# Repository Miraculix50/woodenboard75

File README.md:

# Wooden Keyboard
An ISO-DE 75 % keyboard with a wooden case and knob.

It's definitely not perfect and I'm sure it could be optimized, but for me it's working great.
Feel free to [build it yourself](#parts).

## Parts
### PCB
* [0xcb Helios with MillMax pins and IC-Sockets (MCU) x1](https://keeb.supply/products/0xcb-helios?variant=f57eeaae-cae7-4b2d-b5ac-bef47a280a65)
* [Hotswap sockets x83](https://keeb.supply/products/kailh-hotswap-sockets)
* [THT diodes x84](https://keeb.supply/products/tht-diodes)
* [Reset button x1](https://keeb.supply/products/2-pin-reset-button)
* [EC11 rotary encoder x1](https://keeb.supply/products/pec11r-4220f-s0024)

**Base version:**
* Base-version PCB (when ordering, upload the [gerber files](/pcb/kicad/woodenboard75/production/keyboard.zip))

**RGB version:**
* RGB-version PCB (when ordering, upload the [gerber files](/pcb/kicad/woodenboard75_rgb/production/keyboard.zip))
* SK6812 MINI-E LEDs x83
* 330 Ω resistor x1
* 100 nF capacitor (SMD 0603) x83
* 22 µF capacitor (SMD 1206) x1

### Keys
* [Switches x83](https://keeb.supply/products/invokeys-matcha-reserve-switches)
* [Keycaps for 75%-layout](https://monacokeys.de/products/monacokeys-mk-retro-beige-pbt-keycap-set)

### Wooden case & knob

CAD files are available in the `/cad` folder (`.step` and `.shapr` format).
Pay attention to the different versions, since the RGB-version of the PCB is not compatible with the base version of the bottom case.

* Bar magnets (4mm diameter + 8mm height) x8
* Top case
* Bottom case
* Knob

> All links are just examples.

## Firmware

This keyboard uses the [QMK Firmware](https://qmk.fm). To get started see the [QMK docs](https://docs.qmk.fm/).

Note that you have to copy the contents of `qmk/keyboards/` to your local qmk clone / fork.

## Images

</img> </img> </img> </img> </img> </img> </img> </img>

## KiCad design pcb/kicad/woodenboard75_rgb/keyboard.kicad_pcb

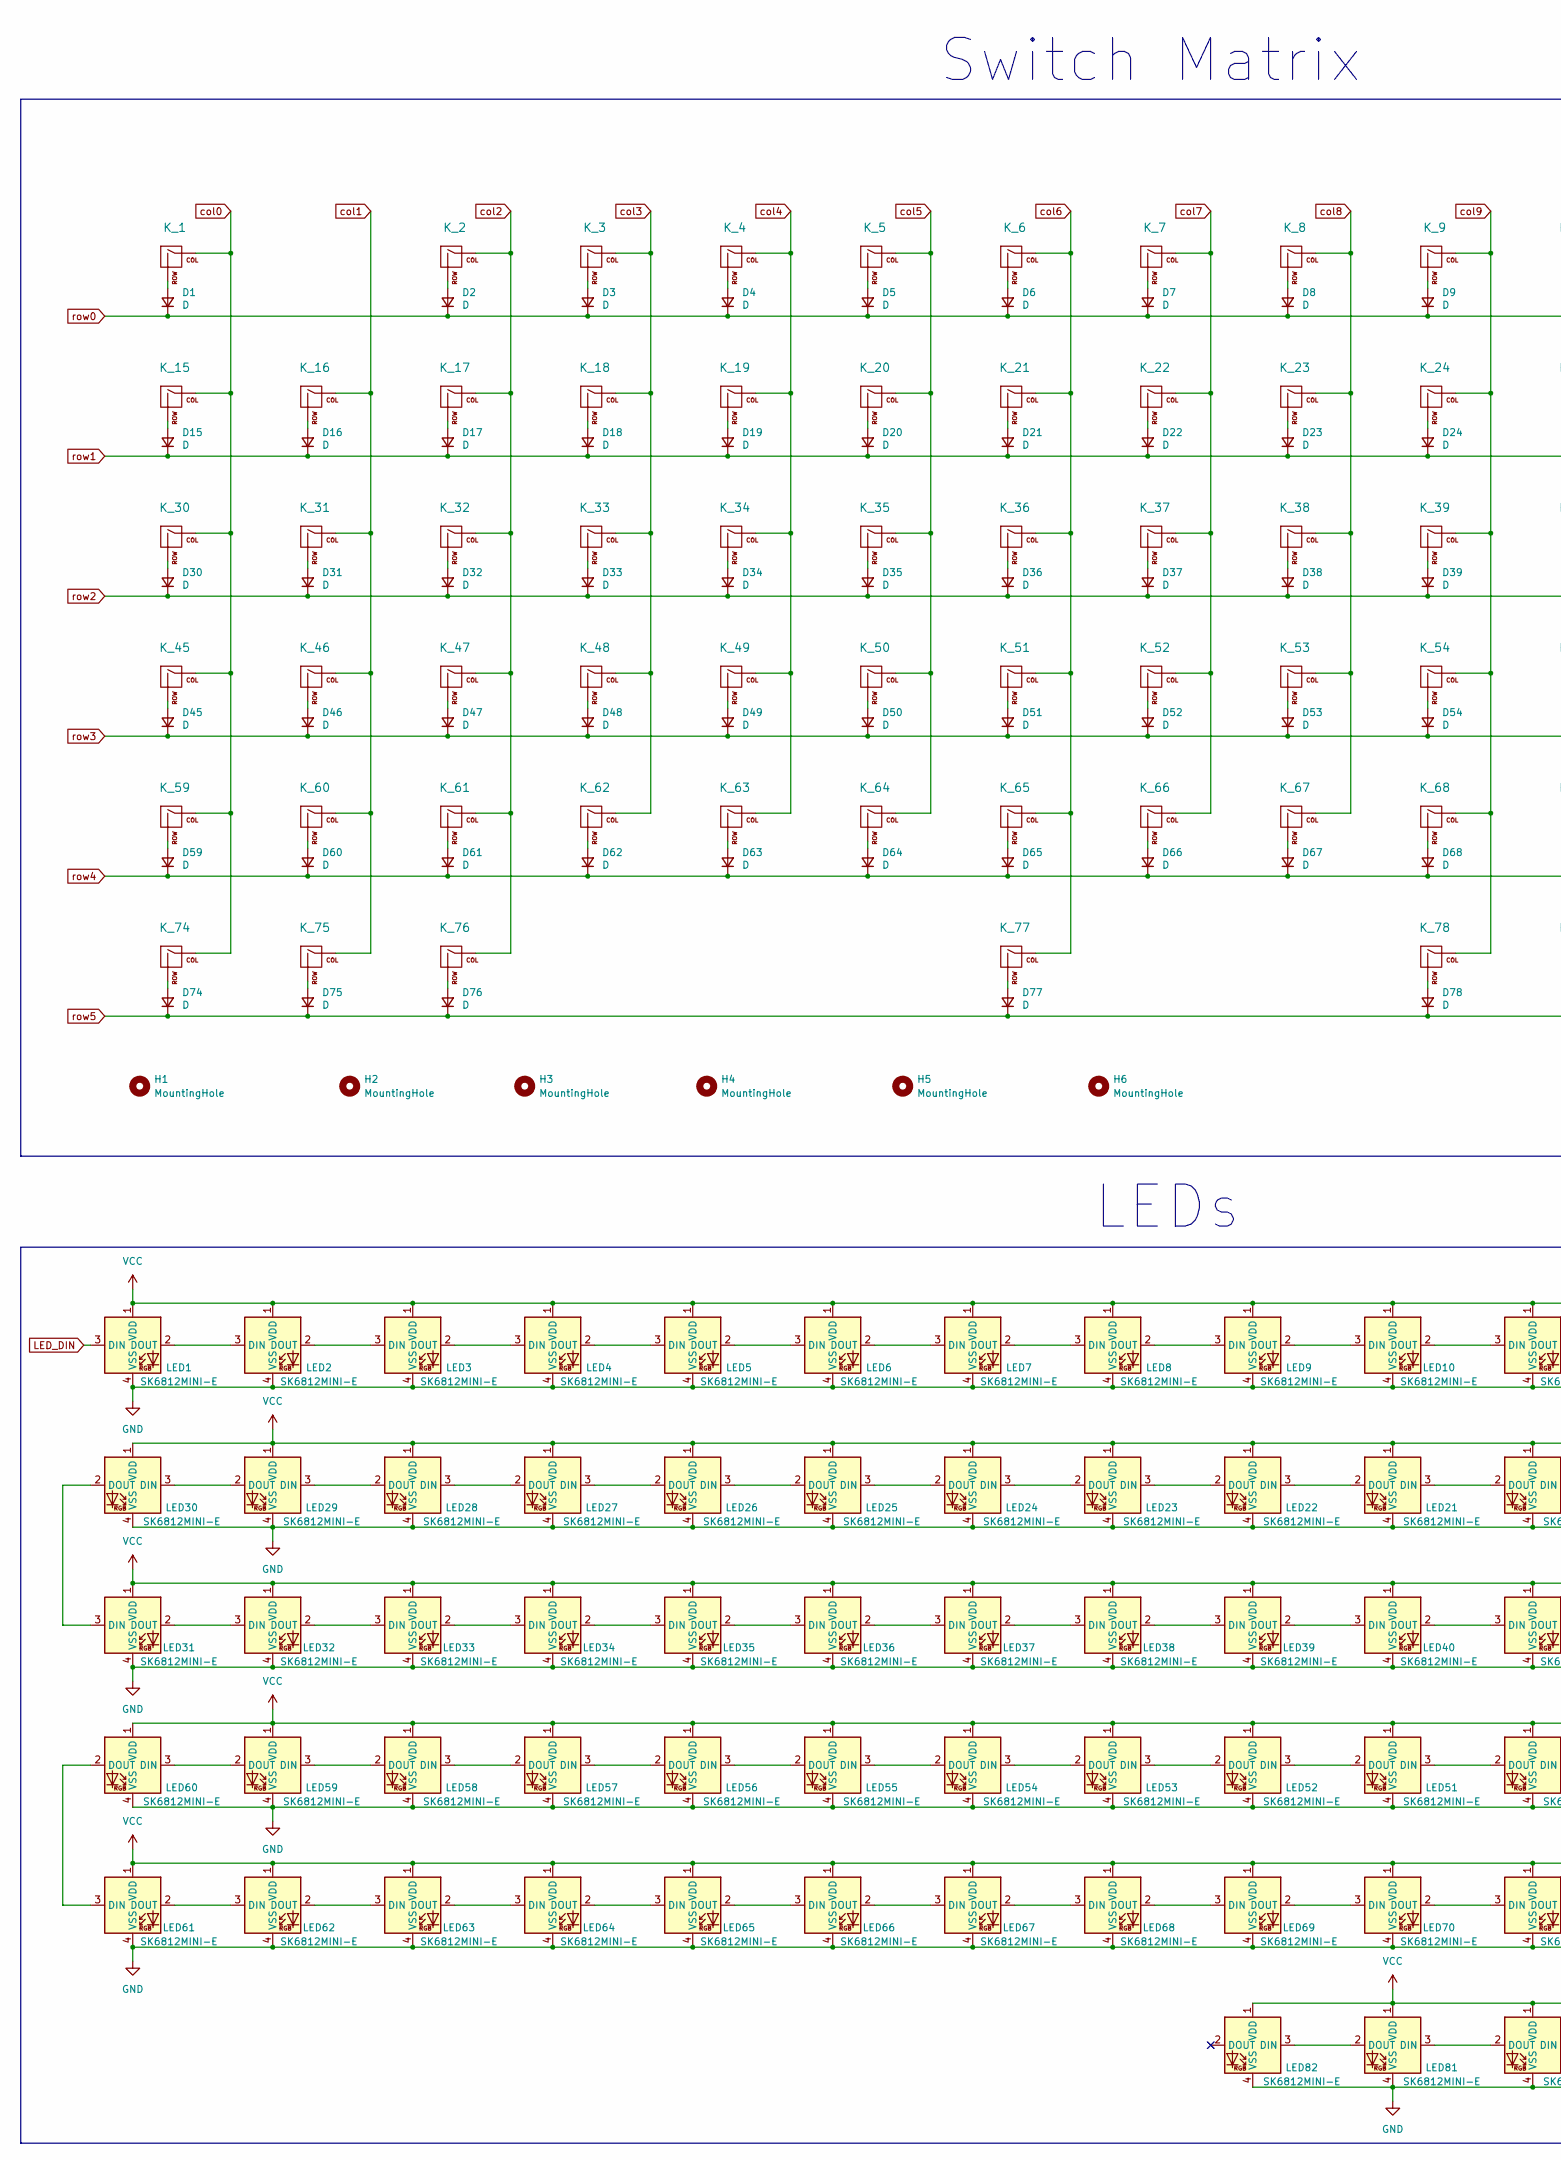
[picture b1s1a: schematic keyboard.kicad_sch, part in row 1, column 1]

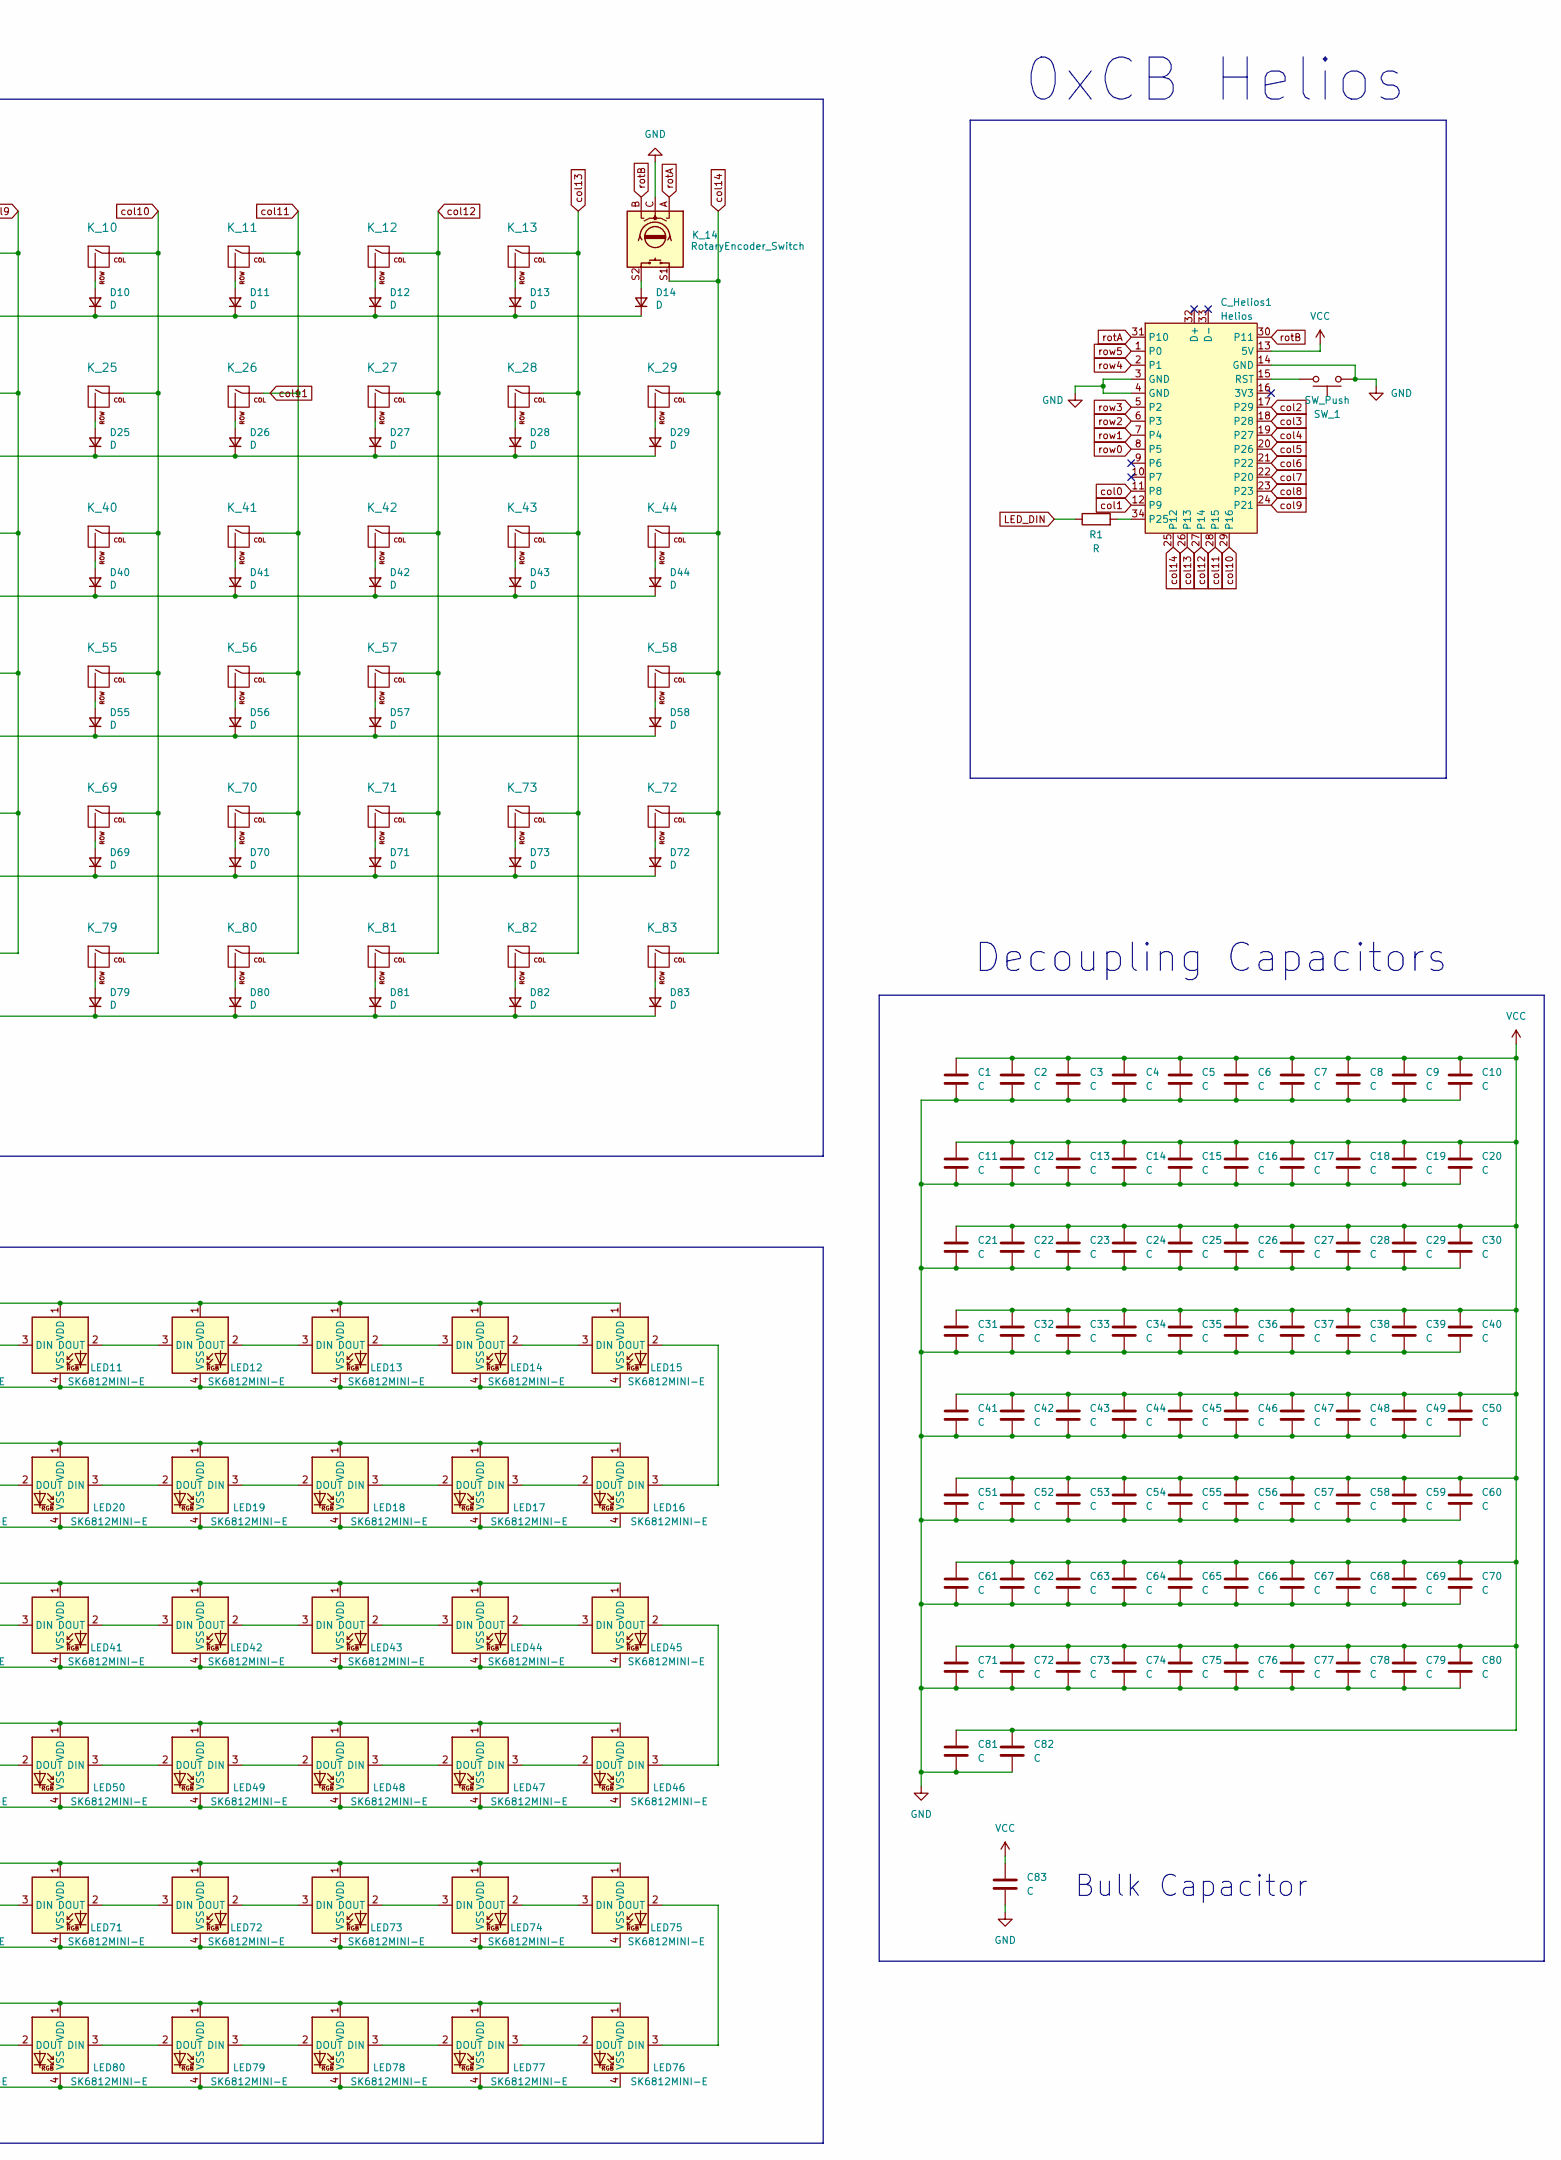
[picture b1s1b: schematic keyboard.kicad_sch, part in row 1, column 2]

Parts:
C1, C2, C3, C4, C5, C6, C7, C8, C9, C10, C11, C12, C13, C14, C15, C16, C17, C18, C19, C20, C21, C22, C23, C24, C25, C26, C27, C28, C29, C30, C31, C32, C33, C34, C35, C36, C37, C38, C39, C40, C41, C42, C43, C44, C45, C46, C47, C48, C49, C50, C51, C52, C53, C54, C55, C56, C57, C58, C59, C60, C61, C62, C63, C64, C65, C66, C67, C68, C69, C70, C71, C72, C73, C74, C75, C76, C77, C78, C79, C80, C81, C82: C; C_0805_2012Metric_Pad1.18x1.45mm_HandSolder
C83: C; C_1206_3216Metric_Pad1.33x1.80mm_HandSolder
C_Helios1: Helios; Helios_AH_USBdn
D1, D2, D3, D4, D5, D6, D7, D8, D9, D10, D11, D12, D13, D14, D15, D16, D17, D18, D19, D20, D21, D22, D23, D24, D25, D26, D27, D28, D29, D30, D31, D32, D33, D34, D35, D36, D37, D38, D39, D40, D41, D42, D43, D44, D45, D46, D47, D48, D49, D50, D51, D52, D53, D54, D55, D56, D57, D58, D59, D60, D61, D62, D63, D64, D65, D66, D67, D68, D69, D70, D71, D72, D73, D74, D75, D76, D77, D78, D79, D80, D81, D82, D83: D; D_DO-35_SOD27_P7.62mm_Horizontal
H1, H2, H3, H4, H5, H6: MountingHole; MountingHole_3.2mm_M3_ISO14580
K_1, K_2, K_3, K_4, K_5, K_6, K_7, K_8, K_9, K_10, K_11, K_12, K_13, K_15, K_16, K_17, K_18, K_19, K_20, K_21, K_22, K_23, K_24, K_25, K_26, K_27, K_29, K_31, K_32, K_33, K_34, K_35, K_36, K_37, K_38, K_39, K_40, K_41, K_42, K_44, K_46, K_47, K_48, K_49, K_50, K_51, K_52, K_53, K_54, K_55, K_56, K_57, K_58, K_60, K_61, K_62, K_63, K_64, K_65, K_66, K_67, K_68, K_69, K_70, K_72, K_73, K_78, K_79, K_80, K_81, K_82, K_83: KEYSW; MX-Hotswap-1U
K_14: RotaryEncoder_Switch; Bourns-PEC11R-4220F-S0024-0-0-0
K_28: KEYSW; MX-Hotswap-2U
K_30: KEYSW; MX-Hotswap-1.5U
K_43: KEYSW; MX-Hotswap-ISO-Rotated
K_45, K_71: KEYSW; MX-Hotswap-1.75U
K_59, K_74, K_75, K_76: KEYSW; MX-Hotswap-1.25U
K_77: KEYSW; MX-Hotswap-6.25U
LED1, LED2, LED3, LED4, LED5, LED6, LED7, LED8, LED9, LED10, LED11, LED12, LED13, LED14, LED15, LED16, LED17, LED18, LED19, LED20, LED21, LED22, LED23, LED24, LED25, LED26, LED27, LED28, LED29, LED30, LED31, LED32, LED33, LED34, LED35, LED36, LED37, LED38, LED39, LED40, LED41, LED42, LED43, LED44, LED45, LED46, LED47, LED48, LED49, LED50, LED51, LED52, LED53, LED54, LED55, LED56, LED57, LED58, LED59, LED60, LED61, LED62, LED63, LED64, LED65, LED66, LED67, LED68, LED69, LED70, LED71, LED72, LED73, LED74, LED75, LED76, LED77, LED78, LED79, LED80, LED81, LED82: SK6812MINI-E; LED_MX_6028R
R1: R; R_Axial_DIN0207_L6.3mm_D2.5mm_P10.16mm_Horizontal
SW_1: SW_Push; SW_PUSH_1P1T_6x3.5mm_H5.0_APEM_MJTP1250

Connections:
GND: C1.2, C2.2, C3.2, C4.2, C5.2, C6.2, C7.2, C8.2, C9.2, C10.2, C11.2, C12.2, C13.2, C14.2, C15.2, C16.2, C17.2, C18.2, C19.2, C20.2, C21.2, C22.2, C23.2, C24.2, C25.2, C26.2, C27.2, C28.2, C29.2, C30.2, C31.2, C32.2, C33.2, C34.2, C35.2, C36.2, C37.2, C38.2, C39.2, C40.2, C41.2, C42.2, C43.2, C44.2, C45.2, C46.2, C47.2, C48.2, C49.2, C50.2, C51.2, C52.2, C53.2, C54.2, C55.2, C56.2, C57.2, C58.2, C59.2, C60.2, C61.2, C62.2, C63.2, C64.2, C65.2, C66.2, C67.2, C68.2, C69.2, C70.2, C71.2, C72.2, C73.2, C74.2, C75.2, C76.2, C77.2, C78.2, C79.2, C80.2, C81.2, C82.2, C83.2, C_Helios1.3 (GND), C_Helios1.4 (GND), C_Helios1.14 (GND), K_14.C, LED1.4 (VSS), LED2.4 (VSS), LED3.4 (VSS), LED4.4 (VSS), LED5.4 (VSS), LED6.4 (VSS), LED7.4 (VSS), LED8.4 (VSS), LED9.4 (VSS), LED10.4 (VSS), LED11.4 (VSS), LED12.4 (VSS), LED13.4 (VSS), LED14.4 (VSS), LED15.4 (VSS), LED16.4 (VSS), LED17.4 (VSS), LED18.4 (VSS), LED19.4 (VSS), LED20.4 (VSS), LED21.4 (VSS), LED22.4 (VSS), LED23.4 (VSS), LED24.4 (VSS), LED25.4 (VSS), LED26.4 (VSS), LED27.4 (VSS), LED28.4 (VSS), LED29.4 (VSS), LED30.4 (VSS), LED31.4 (VSS), LED32.4 (VSS), LED33.4 (VSS), LED34.4 (VSS), LED35.4 (VSS), LED36.4 (VSS), LED37.4 (VSS), LED38.4 (VSS), LED39.4 (VSS), LED40.4 (VSS), LED41.4 (VSS), LED42.4 (VSS), LED43.4 (VSS), LED44.4 (VSS), LED45.4 (VSS), LED46.4 (VSS), LED47.4 (VSS), LED48.4 (VSS), LED49.4 (VSS), LED50.4 (VSS), LED51.4 (VSS), LED52.4 (VSS), LED53.4 (VSS), LED54.4 (VSS), LED55.4 (VSS), LED56.4 (VSS), LED57.4 (VSS), LED58.4 (VSS), LED59.4 (VSS), LED60.4 (VSS), LED61.4 (VSS), LED62.4 (VSS), LED63.4 (VSS), LED64.4 (VSS), LED65.4 (VSS), LED66.4 (VSS), LED67.4 (VSS), LED68.4 (VSS), LED69.4 (VSS), LED70.4 (VSS), LED71.4 (VSS), LED72.4 (VSS), LED73.4 (VSS), LED74.4 (VSS), LED75.4 (VSS), LED76.4 (VSS), LED77.4 (VSS), LED78.4 (VSS), LED79.4 (VSS), LED80.4 (VSS), LED81.4 (VSS), LED82.4 (VSS), SW_1.2
LED_DIN: LED1.3 (DIN), R1.1
unnamed: C_Helios1.34 (P25), R1.2
unnamed: C_Helios1.15 (RST), SW_1.1
unnamed: D1.2 (A), K_1.2 (ROW)
unnamed: D2.2 (A), K_2.2 (ROW)
unnamed: D3.2 (A), K_3.2 (ROW)
unnamed: D4.2 (A), K_4.2 (ROW)
unnamed: D5.2 (A), K_5.2 (ROW)
unnamed: D6.2 (A), K_6.2 (ROW)
unnamed: D7.2 (A), K_7.2 (ROW)
unnamed: D8.2 (A), K_8.2 (ROW)
unnamed: D9.2 (A), K_9.2 (ROW)
unnamed: D10.2 (A), K_10.2 (ROW)
unnamed: D11.2 (A), K_11.2 (ROW)
unnamed: D12.2 (A), K_12.2 (ROW)
unnamed: D13.2 (A), K_13.2 (ROW)
unnamed: D14.2 (A), K_14.S2
unnamed: D15.2 (A), K_15.2 (ROW)
unnamed: D16.2 (A), K_16.2 (ROW)
unnamed: D17.2 (A), K_17.2 (ROW)
unnamed: D18.2 (A), K_18.2 (ROW)
unnamed: D19.2 (A), K_19.2 (ROW)
unnamed: D20.2 (A), K_20.2 (ROW)
unnamed: D21.2 (A), K_21.2 (ROW)
unnamed: D22.2 (A), K_22.2 (ROW)
unnamed: D23.2 (A), K_23.2 (ROW)
unnamed: D24.2 (A), K_24.2 (ROW)
unnamed: D25.2 (A), K_25.2 (ROW)
unnamed: D26.2 (A), K_26.2 (ROW)
unnamed: D27.2 (A), K_27.2 (ROW)
unnamed: D28.2 (A), K_28.2 (ROW)
unnamed: D29.2 (A), K_29.2 (ROW)
unnamed: D30.2 (A), K_30.2 (ROW)
unnamed: D31.2 (A), K_31.2 (ROW)
unnamed: D32.2 (A), K_32.2 (ROW)
unnamed: D33.2 (A), K_33.2 (ROW)
unnamed: D34.2 (A), K_34.2 (ROW)
unnamed: D35.2 (A), K_35.2 (ROW)
unnamed: D36.2 (A), K_36.2 (ROW)
unnamed: D37.2 (A), K_37.2 (ROW)
unnamed: D38.2 (A), K_38.2 (ROW)
unnamed: D39.2 (A), K_39.2 (ROW)
unnamed: D40.2 (A), K_40.2 (ROW)
unnamed: D41.2 (A), K_41.2 (ROW)
unnamed: D42.2 (A), K_42.2 (ROW)
unnamed: D43.2 (A), K_43.2 (ROW)
unnamed: D44.2 (A), K_44.2 (ROW)
unnamed: D45.2 (A), K_45.2 (ROW)
unnamed: D46.2 (A), K_46.2 (ROW)
unnamed: D47.2 (A), K_47.2 (ROW)
unnamed: D48.2 (A), K_48.2 (ROW)
unnamed: D49.2 (A), K_49.2 (ROW)
unnamed: D50.2 (A), K_50.2 (ROW)
unnamed: D51.2 (A), K_51.2 (ROW)
unnamed: D52.2 (A), K_52.2 (ROW)
unnamed: D53.2 (A), K_53.2 (ROW)
unnamed: D54.2 (A), K_54.2 (ROW)
unnamed: D55.2 (A), K_55.2 (ROW)
unnamed: D56.2 (A), K_56.2 (ROW)
unnamed: D57.2 (A), K_57.2 (ROW)
unnamed: D58.2 (A), K_58.2 (ROW)
unnamed: D59.2 (A), K_59.2 (ROW)
unnamed: D60.2 (A), K_60.2 (ROW)
unnamed: D61.2 (A), K_61.2 (ROW)
unnamed: D62.2 (A), K_62.2 (ROW)
unnamed: D63.2 (A), K_63.2 (ROW)
unnamed: D64.2 (A), K_64.2 (ROW)
unnamed: D65.2 (A), K_65.2 (ROW)
unnamed: D66.2 (A), K_66.2 (ROW)
unnamed: D67.2 (A), K_67.2 (ROW)
unnamed: D68.2 (A), K_68.2 (ROW)
unnamed: D69.2 (A), K_69.2 (ROW)
unnamed: D70.2 (A), K_70.2 (ROW)
unnamed: D71.2 (A), K_71.2 (ROW)
unnamed: D72.2 (A), K_72.2 (ROW)
unnamed: D73.2 (A), K_73.2 (ROW)
unnamed: D74.2 (A), K_74.2 (ROW)
unnamed: D75.2 (A), K_75.2 (ROW)
unnamed: D76.2 (A), K_76.2 (ROW)
unnamed: D77.2 (A), K_77.2 (ROW)
unnamed: D78.2 (A), K_78.2 (ROW)
unnamed: D79.2 (A), K_79.2 (ROW)
unnamed: D80.2 (A), K_80.2 (ROW)
unnamed: D81.2 (A), K_81.2 (ROW)
unnamed: D82.2 (A), K_82.2 (ROW)
unnamed: D83.2 (A), K_83.2 (ROW)
unnamed: LED1.2 (DOUT), LED2.3 (DIN)
unnamed: LED2.2 (DOUT), LED3.3 (DIN)
unnamed: LED3.2 (DOUT), LED4.3 (DIN)
unnamed: LED4.2 (DOUT), LED5.3 (DIN)
unnamed: LED5.2 (DOUT), LED6.3 (DIN)
unnamed: LED6.2 (DOUT), LED7.3 (DIN)
unnamed: LED7.2 (DOUT), LED8.3 (DIN)
unnamed: LED8.2 (DOUT), LED9.3 (DIN)
unnamed: LED9.2 (DOUT), LED10.3 (DIN)
unnamed: LED10.2 (DOUT), LED11.3 (DIN)
unnamed: LED11.2 (DOUT), LED12.3 (DIN)
unnamed: LED12.2 (DOUT), LED13.3 (DIN)
unnamed: LED13.2 (DOUT), LED14.3 (DIN)
unnamed: LED14.2 (DOUT), LED15.3 (DIN)
unnamed: LED15.2 (DOUT), LED16.3 (DIN)
unnamed: LED16.2 (DOUT), LED17.3 (DIN)
unnamed: LED17.2 (DOUT), LED18.3 (DIN)
unnamed: LED18.2 (DOUT), LED19.3 (DIN)
unnamed: LED19.2 (DOUT), LED20.3 (DIN)
unnamed: LED20.2 (DOUT), LED21.3 (DIN)
unnamed: LED21.2 (DOUT), LED22.3 (DIN)
unnamed: LED22.2 (DOUT), LED23.3 (DIN)
unnamed: LED23.2 (DOUT), LED24.3 (DIN)
unnamed: LED24.2 (DOUT), LED25.3 (DIN)
unnamed: LED25.2 (DOUT), LED26.3 (DIN)
unnamed: LED26.2 (DOUT), LED27.3 (DIN)
unnamed: LED27.2 (DOUT), LED28.3 (DIN)
unnamed: LED28.2 (DOUT), LED29.3 (DIN)
unnamed: LED29.2 (DOUT), LED30.3 (DIN)
unnamed: LED30.2 (DOUT), LED31.3 (DIN)
unnamed: LED31.2 (DOUT), LED32.3 (DIN)
unnamed: LED32.2 (DOUT), LED33.3 (DIN)
unnamed: LED33.2 (DOUT), LED34.3 (DIN)
unnamed: LED34.2 (DOUT), LED35.3 (DIN)
unnamed: LED35.2 (DOUT), LED36.3 (DIN)
unnamed: LED36.2 (DOUT), LED37.3 (DIN)
unnamed: LED37.2 (DOUT), LED38.3 (DIN)
unnamed: LED38.2 (DOUT), LED39.3 (DIN)
unnamed: LED39.2 (DOUT), LED40.3 (DIN)
unnamed: LED40.2 (DOUT), LED41.3 (DIN)
unnamed: LED41.2 (DOUT), LED42.3 (DIN)
unnamed: LED42.2 (DOUT), LED43.3 (DIN)
unnamed: LED43.2 (DOUT), LED44.3 (DIN)
unnamed: LED44.2 (DOUT), LED45.3 (DIN)
unnamed: LED45.2 (DOUT), LED46.3 (DIN)
unnamed: LED46.2 (DOUT), LED47.3 (DIN)
unnamed: LED47.2 (DOUT), LED48.3 (DIN)
unnamed: LED48.2 (DOUT), LED49.3 (DIN)
unnamed: LED49.2 (DOUT), LED50.3 (DIN)
unnamed: LED50.2 (DOUT), LED51.3 (DIN)
unnamed: LED51.2 (DOUT), LED52.3 (DIN)
unnamed: LED52.2 (DOUT), LED53.3 (DIN)
unnamed: LED53.2 (DOUT), LED54.3 (DIN)
unnamed: LED54.2 (DOUT), LED55.3 (DIN)
unnamed: LED55.2 (DOUT), LED56.3 (DIN)
unnamed: LED56.2 (DOUT), LED57.3 (DIN)
unnamed: LED57.2 (DOUT), LED58.3 (DIN)
unnamed: LED58.2 (DOUT), LED59.3 (DIN)
unnamed: LED59.2 (DOUT), LED60.3 (DIN)
unnamed: LED60.2 (DOUT), LED61.3 (DIN)
unnamed: LED61.2 (DOUT), LED62.3 (DIN)
unnamed: LED62.2 (DOUT), LED63.3 (DIN)
unnamed: LED63.2 (DOUT), LED64.3 (DIN)
unnamed: LED64.2 (DOUT), LED65.3 (DIN)
unnamed: LED65.2 (DOUT), LED66.3 (DIN)
unnamed: LED66.2 (DOUT), LED67.3 (DIN)
unnamed: LED67.2 (DOUT), LED68.3 (DIN)
unnamed: LED68.2 (DOUT), LED69.3 (DIN)
unnamed: LED69.2 (DOUT), LED70.3 (DIN)
unnamed: LED70.2 (DOUT), LED71.3 (DIN)
unnamed: LED71.2 (DOUT), LED72.3 (DIN)
unnamed: LED72.2 (DOUT), LED73.3 (DIN)
unnamed: LED73.2 (DOUT), LED74.3 (DIN)
unnamed: LED74.2 (DOUT), LED75.3 (DIN)
unnamed: LED75.2 (DOUT), LED76.3 (DIN)
unnamed: LED76.2 (DOUT), LED77.3 (DIN)
unnamed: LED77.2 (DOUT), LED78.3 (DIN)
unnamed: LED78.2 (DOUT), LED79.3 (DIN)
unnamed: LED79.2 (DOUT), LED80.3 (DIN)
unnamed: LED80.2 (DOUT), LED81.3 (DIN)
unnamed: LED81.2 (DOUT), LED82.3 (DIN)
VCC: C1.1, C2.1, C3.1, C4.1, C5.1, C6.1, C7.1, C8.1, C9.1, C10.1, C11.1, C12.1, C13.1, C14.1, C15.1, C16.1, C17.1, C18.1, C19.1, C20.1, C21.1, C22.1, C23.1, C24.1, C25.1, C26.1, C27.1, C28.1, C29.1, C30.1, C31.1, C32.1, C33.1, C34.1, C35.1, C36.1, C37.1, C38.1, C39.1, C40.1, C41.1, C42.1, C43.1, C44.1, C45.1, C46.1, C47.1, C48.1, C49.1, C50.1, C51.1, C52.1, C53.1, C54.1, C55.1, C56.1, C57.1, C58.1, C59.1, C60.1, C61.1, C62.1, C63.1, C64.1, C65.1, C66.1, C67.1, C68.1, C69.1, C70.1, C71.1, C72.1, C73.1, C74.1, C75.1, C76.1, C77.1, C78.1, C79.1, C80.1, C81.1, C82.1, C83.1, C_Helios1.13 (5V), LED1.1 (VDD), LED2.1 (VDD), LED3.1 (VDD), LED4.1 (VDD), LED5.1 (VDD), LED6.1 (VDD), LED7.1 (VDD), LED8.1 (VDD), LED9.1 (VDD), LED10.1 (VDD), LED11.1 (VDD), LED12.1 (VDD), LED13.1 (VDD), LED14.1 (VDD), LED15.1 (VDD), LED16.1 (VDD), LED17.1 (VDD), LED18.1 (VDD), LED19.1 (VDD), LED20.1 (VDD), LED21.1 (VDD), LED22.1 (VDD), LED23.1 (VDD), LED24.1 (VDD), LED25.1 (VDD), LED26.1 (VDD), LED27.1 (VDD), LED28.1 (VDD), LED29.1 (VDD), LED30.1 (VDD), LED31.1 (VDD), LED32.1 (VDD), LED33.1 (VDD), LED34.1 (VDD), LED35.1 (VDD), LED36.1 (VDD), LED37.1 (VDD), LED38.1 (VDD), LED39.1 (VDD), LED40.1 (VDD), LED41.1 (VDD), LED42.1 (VDD), LED43.1 (VDD), LED44.1 (VDD), LED45.1 (VDD), LED46.1 (VDD), LED47.1 (VDD), LED48.1 (VDD), LED49.1 (VDD), LED50.1 (VDD), LED51.1 (VDD), LED52.1 (VDD), LED53.1 (VDD), LED54.1 (VDD), LED55.1 (VDD), LED56.1 (VDD), LED57.1 (VDD), LED58.1 (VDD), LED59.1 (VDD), LED60.1 (VDD), LED61.1 (VDD), LED62.1 (VDD), LED63.1 (VDD), LED64.1 (VDD), LED65.1 (VDD), LED66.1 (VDD), LED67.1 (VDD), LED68.1 (VDD), LED69.1 (VDD), LED70.1 (VDD), LED71.1 (VDD), LED72.1 (VDD), LED73.1 (VDD), LED74.1 (VDD), LED75.1 (VDD), LED76.1 (VDD), LED77.1 (VDD), LED78.1 (VDD), LED79.1 (VDD), LED80.1 (VDD), LED81.1 (VDD), LED82.1 (VDD)
col0: C_Helios1.11 (P8), K_1.1 (COL), K_15.1 (COL), K_30.1 (COL), K_45.1 (COL), K_59.1 (COL), K_74.1 (COL)
col1: C_Helios1.12 (P9), K_16.1 (COL), K_31.1 (COL), K_46.1 (COL), K_60.1 (COL), K_75.1 (COL)
col2: C_Helios1.17 (P29), K_2.1 (COL), K_17.1 (COL), K_32.1 (COL), K_47.1 (COL), K_61.1 (COL), K_76.1 (COL)
col3: C_Helios1.18 (P28), K_3.1 (COL), K_18.1 (COL), K_33.1 (COL), K_48.1 (COL), K_62.1 (COL)
col4: C_Helios1.19 (P27), K_4.1 (COL), K_19.1 (COL), K_34.1 (COL), K_49.1 (COL), K_63.1 (COL)
col5: C_Helios1.20 (P26), K_5.1 (COL), K_20.1 (COL), K_35.1 (COL), K_50.1 (COL), K_64.1 (COL)
col6: C_Helios1.21 (P22), K_6.1 (COL), K_21.1 (COL), K_36.1 (COL), K_51.1 (COL), K_65.1 (COL), K_77.1 (COL)
col7: C_Helios1.22 (P20), K_7.1 (COL), K_22.1 (COL), K_37.1 (COL), K_52.1 (COL), K_66.1 (COL)
col8: C_Helios1.23, K_8.1 (COL), K_23.1 (COL), K_38.1 (COL), K_53.1 (COL), K_67.1 (COL)
col9: C_Helios1.24 (P21), K_9.1 (COL), K_24.1 (COL), K_39.1 (COL), K_54.1 (COL), K_68.1 (COL), K_78.1 (COL)
col10: C_Helios1.29 (P16), K_10.1 (COL), K_25.1 (COL), K_40.1 (COL), K_55.1 (COL), K_69.1 (COL), K_79.1 (COL)
col11: C_Helios1.28 (P15), K_11.1 (COL), K_26.1 (COL), K_41.1 (COL), K_56.1 (COL), K_70.1 (COL), K_80.1 (COL)
col12: C_Helios1.27 (P14), K_12.1 (COL), K_27.1 (COL), K_42.1 (COL), K_57.1 (COL), K_71.1 (COL), K_81.1 (COL)
col13: C_Helios1.26 (P13), K_13.1 (COL), K_28.1 (COL), K_43.1 (COL), K_73.1 (COL), K_82.1 (COL)
col14: C_Helios1.25 (P12), K_14.S1, K_29.1 (COL), K_44.1 (COL), K_58.1 (COL), K_72.1 (COL), K_83.1 (COL)
rotA: C_Helios1.31 (P10), K_14.A
rotB: C_Helios1.30 (P11), K_14.B
row0: C_Helios1.8 (P5), D1.1 (K), D2.1 (K), D3.1 (K), D4.1 (K), D5.1 (K), D6.1 (K), D7.1 (K), D8.1 (K), D9.1 (K), D10.1 (K), D11.1 (K), D12.1 (K), D13.1 (K), D14.1 (K)
row1: C_Helios1.7 (P4), D15.1 (K), D16.1 (K), D17.1 (K), D18.1 (K), D19.1 (K), D20.1 (K), D21.1 (K), D22.1 (K), D23.1 (K), D24.1 (K), D25.1 (K), D26.1 (K), D27.1 (K), D28.1 (K), D29.1 (K)
row2: C_Helios1.6 (P3), D30.1 (K), D31.1 (K), D32.1 (K), D33.1 (K), D34.1 (K), D35.1 (K), D36.1 (K), D37.1 (K), D38.1 (K), D39.1 (K), D40.1 (K), D41.1 (K), D42.1 (K), D43.1 (K), D44.1 (K)
row3: C_Helios1.5 (P2), D45.1 (K), D46.1 (K), D47.1 (K), D48.1 (K), D49.1 (K), D50.1 (K), D51.1 (K), D52.1 (K), D53.1 (K), D54.1 (K), D55.1 (K), D56.1 (K), D57.1 (K), D58.1 (K)
row4: C_Helios1.2 (P1), D59.1 (K), D60.1 (K), D61.1 (K), D62.1 (K), D63.1 (K), D64.1 (K), D65.1 (K), D66.1 (K), D67.1 (K), D68.1 (K), D69.1 (K), D70.1 (K), D71.1 (K), D72.1 (K), D73.1 (K)
row5: C_Helios1.1 (P0), D74.1 (K), D75.1 (K), D76.1 (K), D77.1 (K), D78.1 (K), D79.1 (K), D80.1 (K), D81.1 (K), D82.1 (K), D83.1 (K)

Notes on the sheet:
Bulk Capacitor
LEDs
Decoupling Capacitors
Switch Matrix
0xCB Helios

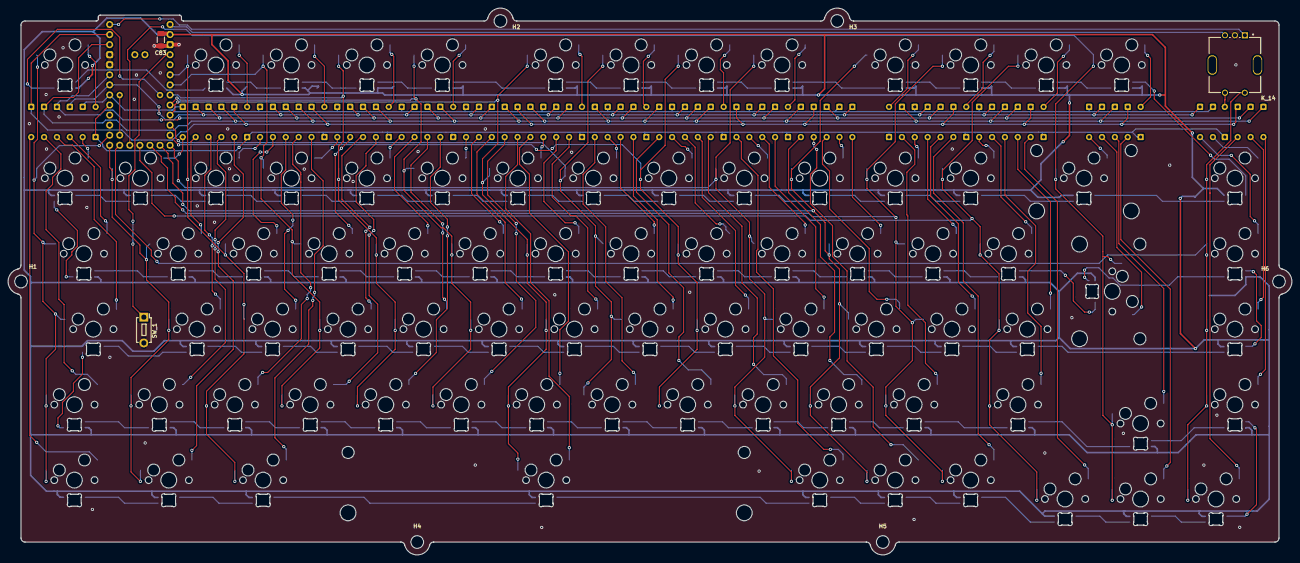
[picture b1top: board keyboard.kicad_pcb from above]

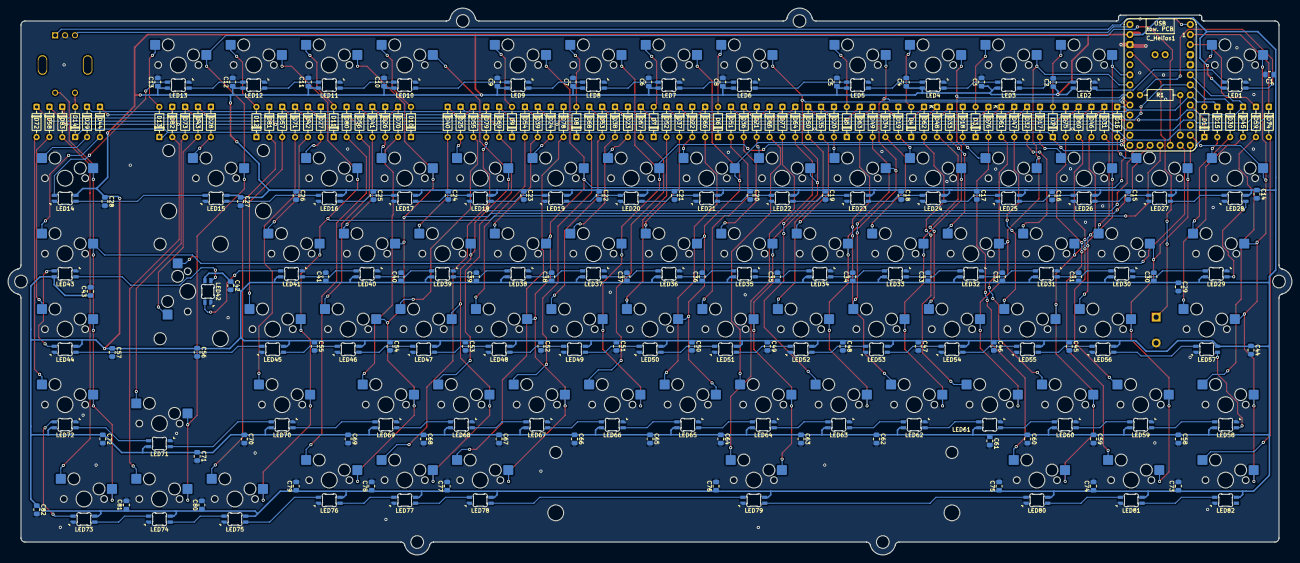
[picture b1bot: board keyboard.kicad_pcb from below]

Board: 2 copper layers, 324.0 x 138.0 mm, 340 parts (331 on the bottom side), 192 nets.

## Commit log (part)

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2026-01-29 Add .gitignore
2026-01-29 Update parts list
2026-01-29 Added MIT License
